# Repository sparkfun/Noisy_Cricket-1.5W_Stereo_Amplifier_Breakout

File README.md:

SparkFun Noisy Cricket Stereo Amplifier - 1.5W
==========================================

[*SparkFun Noisy Cricket Stereo Amplifier - 1.5W (DEV-14475)*](https://www.sparkfun.com/products/14475)

The Noisy Cricket is a 300mW stereo amplifier which can be configured to output up to 1.5W of mono amplification.
With a dual-gang pot you can control the volume with a single pot, as well as turn power on and off!

Repository Contents
-------------------
* **/Hardware** - All Eagle design files (.brd, .sch)
* **/Production** - Test bed files and production panel files

Documentation
--------------
* **[Hookup Guide](https://learn.sparkfun.com/tutorials/noisy-cricket-stereo-amplifier---15w-hookup-guide)** - Basic hookup guide for the Noisy Cricket.

License Information
-------------------

This product is _**open source**_! 

Please review the LICENSE.md file for license information. 

If you have any questions or concerns on licensing, please contact techsupport@sparkfun.com.

Distributed as-is; no warranty is given.

- Your friends at SparkFun.

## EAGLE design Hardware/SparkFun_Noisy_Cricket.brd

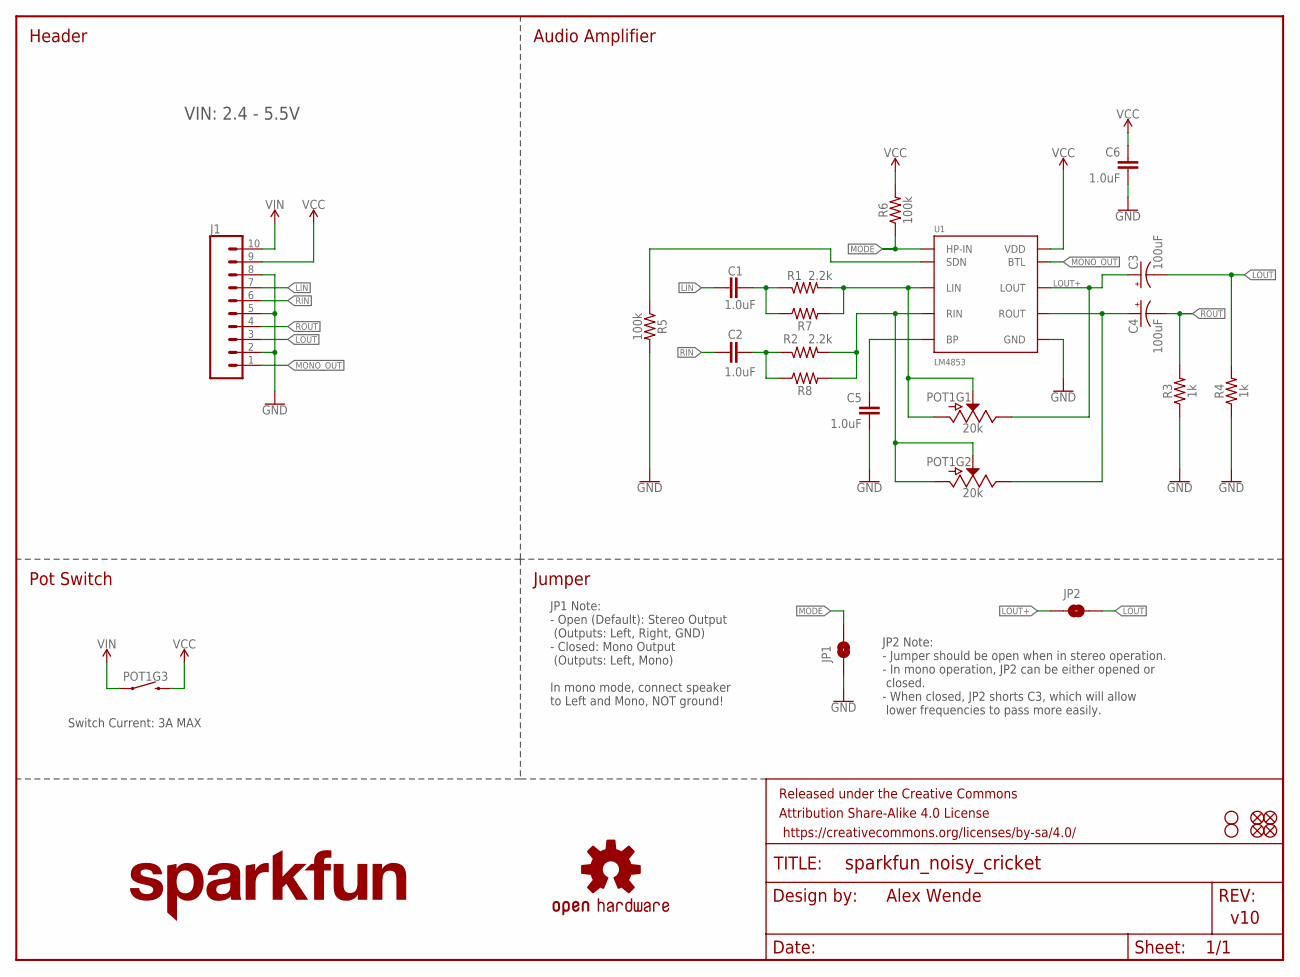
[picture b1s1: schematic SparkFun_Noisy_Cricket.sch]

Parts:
C1, C2, C5, C6: 1.0uF; 0603
C3, C4: 100uF; PANASONIC_D
FD1, FD2, FD3, FD4: FIDUCIALUFIDUCIAL; FIDUCIAL-MICRO
FRAME1: FRAME-LETTER; CREATIVE_COMMONS
H1, H2: STAND-OFF
J1: CONN_10NO_SILK_PTH_FEMALE; 1X10_NO_SILK
JP1, JP2: JUMPER-SMT_2_NO_NO-SILK; SMT-JUMPER_2_NO_NO-SILK
LOGO1: SFE_LOGO_NAME.1_INCH; SFE_LOGO_NAME_.1
LOGO2: OSHW-LOGOS; OSHW-LOGO-S
POT1: 20k; POT-DUAL-SWITCH-PTH
R1, R2: 2.2k; 0603
R3, R4: 1k; 0603
R5, R6: 100k; 0603
R7, R8: AXIAL-0.3-KIT
U1: LM4853; TFSOP-10

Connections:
5V: C6.1, J1.9, POT1.SW2 (2), R6.2, U1.VDD
GND: C5.2, C6.2, J1.2, J1.5, J1.8, JP1.1, R3.1, R4.1, R5.2, U1.GND
LIN: C1.1, J1.7
LOUT: C3.-, J1.3, JP2.2, R4.2
LOUT+: C3.+, JP2.1, POT1.A3 (E), U1.LOUT
MODE: JP1.2, R6.1, U1.HP-IN
MONO_OUT: J1.1, U1.BTL
unnamed: C1.2, R1.1, R7.P$1 (1)
unnamed: C5.1, U1.BP
unnamed: C2.2, R2.1, R8.P$1 (1)
unnamed: R5.1, U1.SDN
unnamed: C4.+, POT1.B3 (E), U1.ROUT
unnamed: POT1.A1 (A), POT1.A2 (S), R1.2, R7.P$2 (2), U1.LIN
unnamed: POT1.B1 (A), POT1.B2 (S), R2.2, R8.P$2 (2), U1.RIN
RIN: C2.1, J1.6
ROUT: C4.-, J1.4, R3.2
VIN: J1.10, POT1.SW1 (1)

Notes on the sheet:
JP1 Note: - Open (Default): Stereo Output (Outputs: Left, Right, GND) - Closed: Mono Output (Outputs: Left, Mono) In mono mode, connect speaker to Left and Mono, NOT ground!
Jumper
Audio Amplifier
Header
Pot Switch
Alex Wende
v10
VIN: 2.4 - 5.5V
Switch Current: 3A MAX
JP2 Note: - Jumper should be open when in stereo operation. - In mono operation, JP2 can be either opened or closed. - When closed, JP2 shorts C3, which will allow lower frequencies to pass more easily.

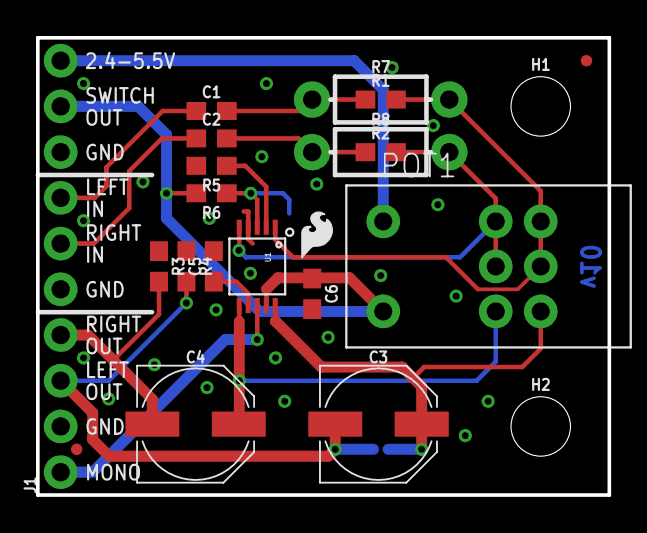
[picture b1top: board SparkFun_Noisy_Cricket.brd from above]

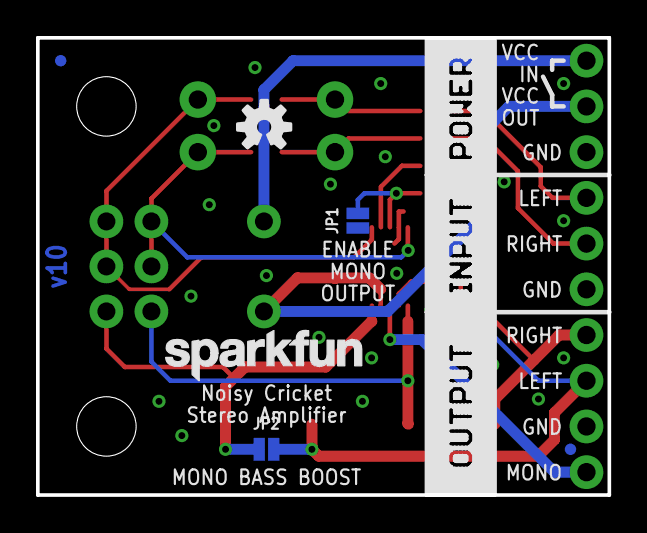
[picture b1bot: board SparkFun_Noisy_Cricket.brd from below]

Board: 2 copper layers, 31.8 x 25.4 mm, 29 parts (6 on the bottom side), 17 nets.

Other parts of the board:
U$1: SFE_LOGO_FLAME_.1

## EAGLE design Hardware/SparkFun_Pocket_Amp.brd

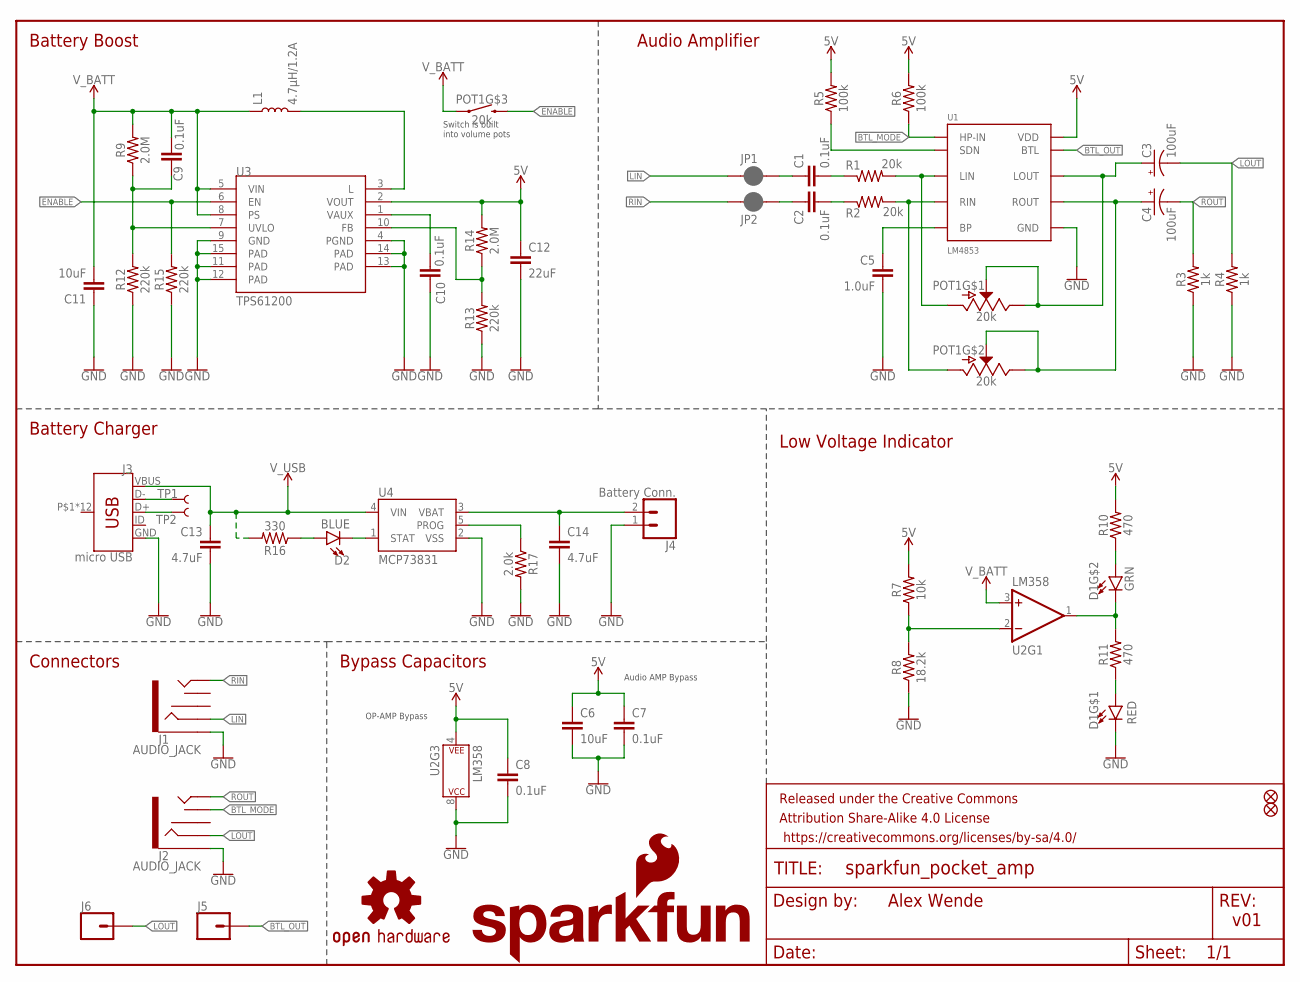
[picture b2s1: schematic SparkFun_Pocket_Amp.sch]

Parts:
C1, C2: 0.1uF; CAP-PTH-SMALL-KIT
C3, C4: 100uF; CPOL-RADIAL-2.5MM-6.5MM
C5: 1.0uF; 0603
C6, C11: 10uF; 0805
C7, C8, C9, C10: 0.1uF; 0603
C12: 22uF; 1210
C13, C14: 4.7uF; 0603
D1: LED Inicator; LED_3MM_RG_SMD
D2: BLUE; LED-0603
FD1, FD2: FIDUCIALUFIDUCIAL; FIDUCIAL-MICRO
FRAME1: FRAME-LETTER; CREATIVE_COMMONS
J1, J2: AUDIO_JACK; AUDIO-JACK-3.5MM-SMD
J3: micro USB; USB-MICROB-PTH
J4: Battery Conn.; JST-2-SMD
J5, J6: CONN_01PTH_NO_SILK_KIT; 1X01NS_KIT
JP1, JP2: JUMPER-SMT_2_NC_PASTE_NO-SILK; SMT-JUMPER_2_NC_PASTE_NO-SILK
L1: 4.7µH/1.2A; INDUCTOR_4.7UH
LOGO1: SFE_LOGO_NAME_FLAME.1_INCH; SFE_LOGO_NAME_FLAME_.1
LOGO2: OSHW-LOGOM; OSHW-LOGO-M
POT1: 20k; POT-DUAL-SWITCH-PTH
R1, R2: 20k; AXIAL-0.3-KIT
R3, R4: 1k; AXIAL-0.3-KIT
R5, R6: 100k; AXIAL-0.3-KIT
R7: 10k; AXIAL-0.3-KIT
R8: 18.2k; AXIAL-0.3-KIT
R9, R14: 2.0M; 0603
R10, R11: 470; AXIAL-0.3-KIT
R12, R13, R15: 220k; 0603
R16: 330; 0603
R17: 2.0k; 0603
TP1, TP2: TEST-POINT3; PAD.03X.03
U1: LM4853; TFSOP-10
U2: LM358; DIP08-KIT
U3: TPS61200; QFN-10_PAD
U4: MCP73831; SOT23-5

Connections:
5V: C6.1, C7.1, C8.1, C12.1, R5.P$2 (2), R6.P$2 (2), R7.P$2 (2), R10.P$2 (2), R14.2, U1.VDD, U2.4 (P$V-), U3.2 (VOUT)
BTL_MODE: J2.TSH, R6.P$1 (1), U1.HP-IN
BTL_OUT: J5.1, U1.BTL
ENABLE: POT1.SW2 (2), R15.2, U3.6 (EN)
GND: C5.2, C6.2, C7.2, C8.2, C10.1, C11.1, C12.2, C13.2, C14.2, D1.1 (C), J1.SLEEVE, J2.SLEEVE, J3.GND, J4.1 (2), R3.P$1 (1), R4.P$1 (1), R8.P$1 (1), R12.1, R13.1, R15.1, R17.2, U1.GND, U2.8 (P$V+), U3.4 (PGND), U3.9 (GND), U3.11 (PAD), U3.12 (PAD), U3.13 (PAD), U3.14 (PAD), U3.15 (PAD), U4.2 (VSS)
IN_L: C1.1, JP1.2
IN_R: C2.1, JP2.2
LIN: J1.RING, JP1.1
LOUT: C3.2 (-), J2.RING, J6.1, R4.P$2 (2)
unnamed: POT1.A1 (A), R1.P$2 (2), U1.LIN
unnamed: POT1.B1 (A), R2.P$2 (2), U1.RIN
unnamed: C1.2, R1.P$1 (1)
unnamed: C2.2, R2.P$1 (1)
unnamed: C5.1, U1.BP
unnamed: R7.P$1 (1), R8.P$2 (2), U2.2 (-IN)
unnamed: C9.1, R9.1, R12.2, U3.7 (UVLO)
unnamed: C3.1 (+), POT1.A2 (E), POT1.A3 (S), U1.LOUT
unnamed: R5.P$1 (1), U1.SDN
unnamed: J3.D-, TP1.P$1
unnamed: D1.3 (A), R10.P$1 (1)
unnamed: C4.1 (+), POT1.B2 (E), POT1.B3 (S), U1.ROUT
unnamed: D1.2 (A), R11.P$1 (1)
unnamed: D2.C, U4.1 (STAT)
unnamed: D2.A, R16.1
unnamed: L1.P$2 (2), U3.3 (L)
unnamed: D1.4 (C), R11.P$2 (2), U2.1 (OUT)
unnamed: J3.D+, TP2.P$1
unnamed: C10.2, U3.1 (VAUX)
unnamed: R13.2, R14.1, U3.10 (FB)
unnamed: C14.1, J4.2 (1), U4.3 (VBAT)
unnamed: R17.1, U4.5 (PROG)
RIN: J1.TIP, JP2.1
ROUT: C4.2 (-), J2.TIP, R3.P$2 (2)
V_BATT: C9.2, C11.2, L1.P$1 (1), POT1.SW1 (1), R9.2, U2.3 (+IN), U3.5 (VIN), U3.8 (PS)
V_USB: C13.1, J3.VBUS, R16.2, U4.4 (VIN)

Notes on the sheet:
RED
GRN
Battery Boost
Audio Amplifier
Low Voltage Indicator
Battery Charger
Alex Wende
v01
Switch is built into volume pots
Connectors
Bypass Capacitors
OP-AMP Bypass
Audio AMP Bypass

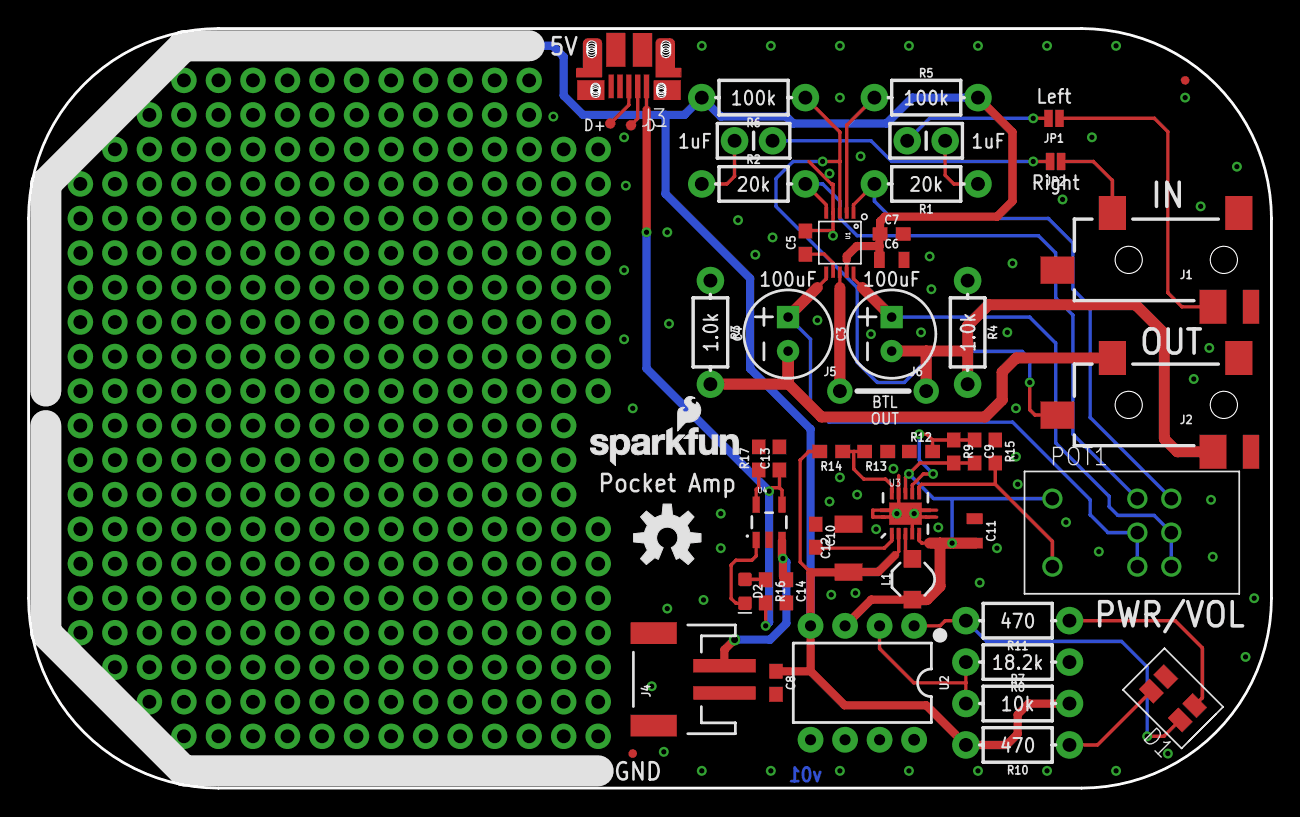
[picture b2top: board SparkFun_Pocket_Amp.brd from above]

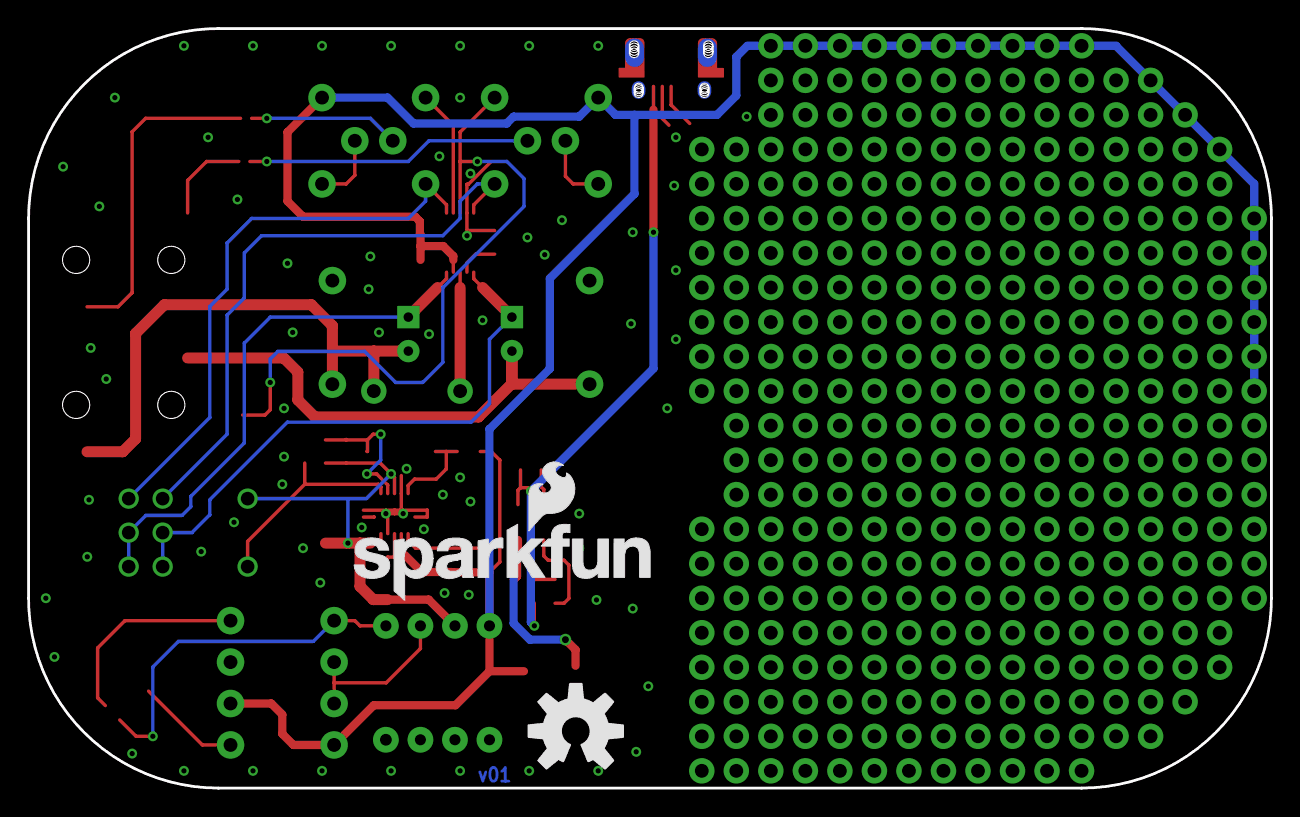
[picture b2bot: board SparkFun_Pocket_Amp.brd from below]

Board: 2 copper layers, 91.4 x 55.9 mm, 56 parts (2 on the bottom side), 35 nets.

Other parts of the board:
U$1: SFE_LOGO_NAME_FLAME_.2
U$2: OSHW-LOGO-L

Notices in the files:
parts and their libraries:
SparkFun-Capacitors: Licensing: Creative Commons ShareAlike 4.0 International - https://creativecommons.org/licenses/by-sa/4.0
SparkFun-Aesthetics: Released under the Creative Commons Attribution Share-Alike 4.0 License
SparkFun-Aesthetics: https://creativecommons.org/licenses/by-sa/4.0
